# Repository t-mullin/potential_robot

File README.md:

View this project on [CADLAB.io](https://cadlab.io/project/25201). 

# potential_robot
This is repo is to test CADLAB integration and Collaboration

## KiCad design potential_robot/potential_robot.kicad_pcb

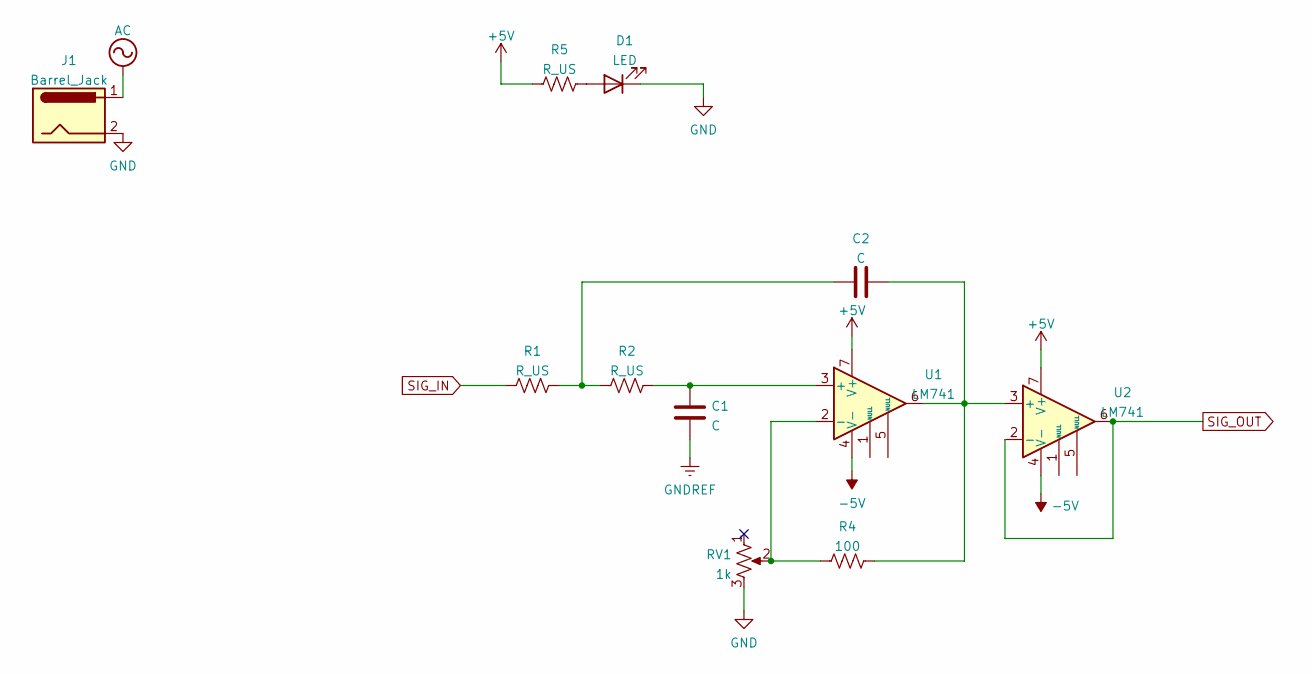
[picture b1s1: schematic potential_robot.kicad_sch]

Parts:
C1, C2: C; C_Disc_D4.3mm_W1.9mm_P5.00mm
D1: LED; LED_0805_2012Metric
J1: Barrel_Jack; BarrelJack_Wuerth_6941xx301002
R1, R2, R5: R_US; R_Axial_DIN0207_L6.3mm_D2.5mm_P7.62mm_Horizontal
R4: 100; R_Axial_DIN0207_L6.3mm_D2.5mm_P7.62mm_Horizontal
RV1: 1k; Potentiometer_ACP_CA6-H2,5_Horizontal
U1, U2: LM741; DIP-8_W7.62mm_Socket

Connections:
+5V: R5.1, U1.7 (V+), U2.7 (V+)
-5V: U1.4 (V-), U2.4 (V-)
AC: J1.1
GND: D1.1 (K), J1.2, RV1.3
GNDREF: C1.2
unnamed: C1.1, R2.2, U1.3 (+)
unnamed: C2.1, R1.2, R2.1
unnamed: C2.2, R4.2, U1.6, U2.3 (+)
unnamed: D1.2 (A), R5.2
unnamed: R4.1, RV1.2, U1.2 (-)
SIG_IN: R1.1
SIG_OUT: U2.2 (-), U2.6

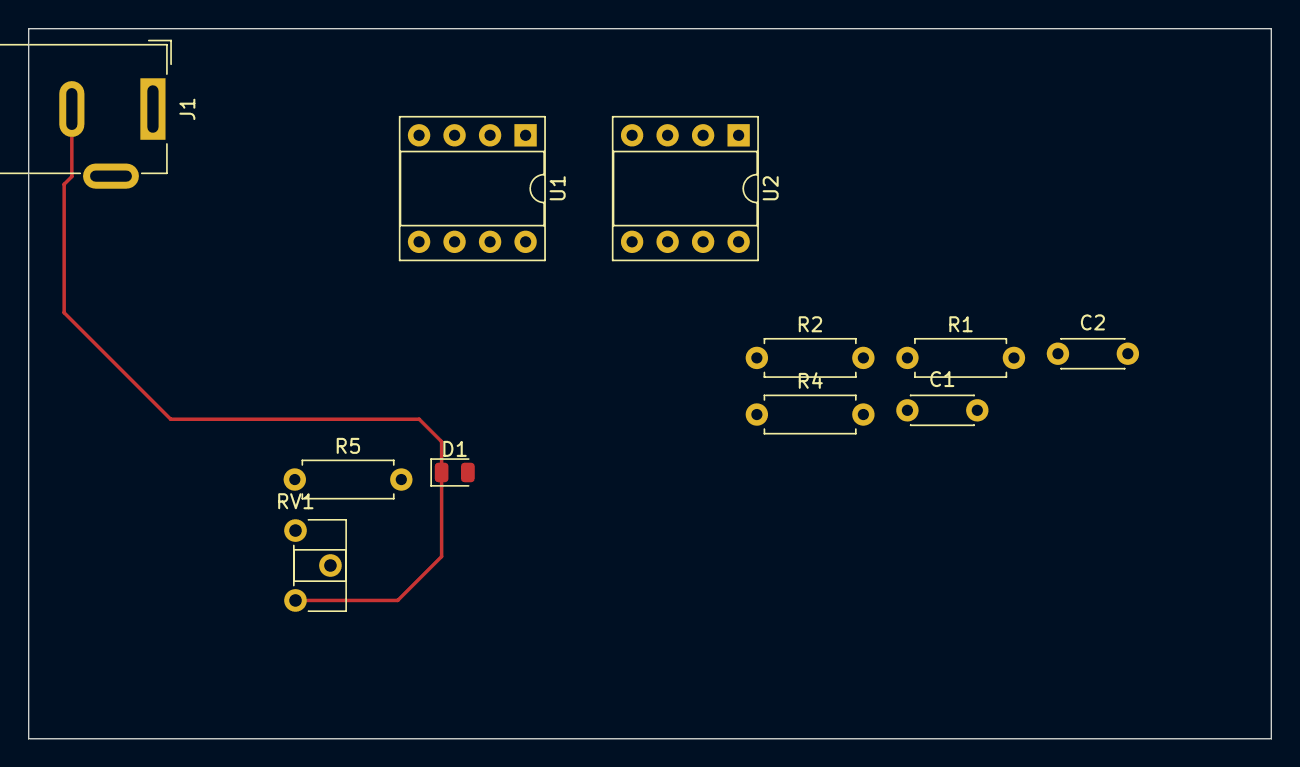
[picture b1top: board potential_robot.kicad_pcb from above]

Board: 2 copper layers, 88.9 x 50.8 mm, 11 parts (0 on the bottom side), 9 nets.

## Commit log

2022-02-09 Backlink to CADLAB.io has been added.
2022-02-09 initial design for a SK Filter. pcb needs to be laid out
2022-02-10 Replaced a resistor with a pot for volume control. Added a power jack, rectifier and smoother TBD.
2022-02-10 added edge cut to pcb
2022-02-10 added a trace
